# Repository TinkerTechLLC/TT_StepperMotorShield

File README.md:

# TT_StepperMotorShield
This stepper motor shield is capable of smooth, simultaneous control of two bi-polar stepper using [Allegro A4988 
stepper driver breakout sticks](https://www.pololu.com/product/1182). It also has a handy mounting location for an 
[XBee radio adapter board](https://www.adafruit.com/products/126). Use caution when using the XBee radio at the 
same time as the motors. It has been found to cause hiccups in the motors step interrupts, so this can cause the motors
to stall when running at higher speeds.

Order boards here: https://oshpark.com/shared_projects/M8zwapGA

Library for controller shield via Arduino Uno: https://github.com/TinkerTechLLC/TT_StepperMotorShield_Library

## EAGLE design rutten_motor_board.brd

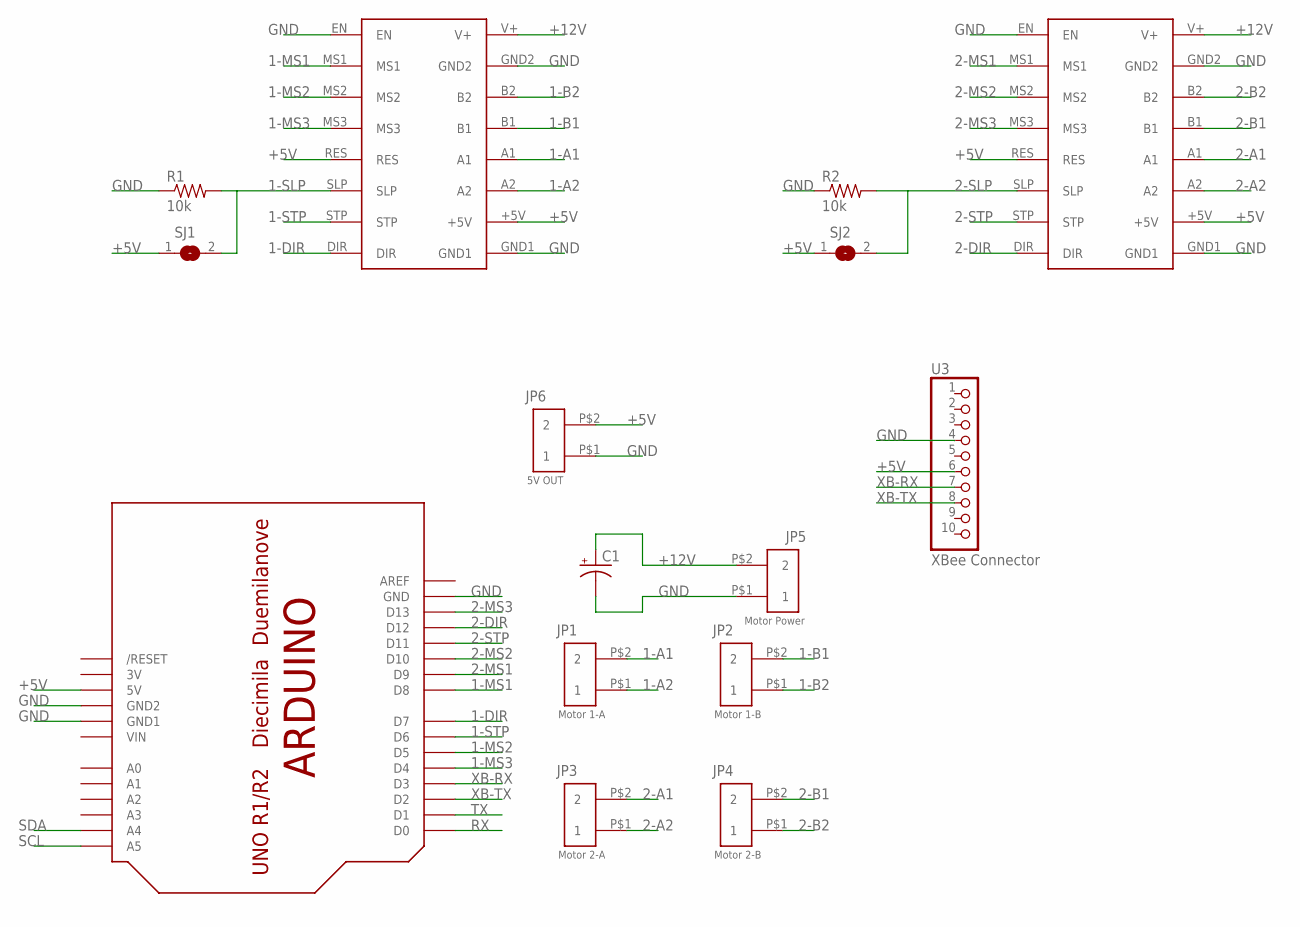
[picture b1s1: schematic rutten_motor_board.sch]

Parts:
C1: CAP_POLPTH2; CPOL-RADIAL-10UF-25V
JP1: Motor 1-A; SCREW_TERM-200MIL-2
JP2: Motor 1-B; SCREW_TERM-200MIL-2
JP3: Motor 2-A; SCREW_TERM-200MIL-2
JP4: Motor 2-B; SCREW_TERM-200MIL-2
JP5: Motor Power; SCREW_TERM-200MIL-2
JP6: 5V OUT; SCREW_TERM-200MIL-2
R1, R2: 10k; AXIAL-0.4
SJ1, SJ2: SJ
U1, U2: A4988_STEP_STICK; A9488_STEP_STICK
U3: XBee Connector; 1X10-BIG
U$1: ARDUINOUNO; ARDUINO

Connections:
1-A1: JP1.P$2 (2), U1.A1
1-A2: JP1.P$1 (1), U1.A2
1-B1: JP2.P$2 (2), U1.B1
1-B2: JP2.P$1 (1), U1.B2
1-DIR: U1.DIR, U$1.D7
1-MS1: U1.MS1, U$1.D8
1-MS2: U1.MS2, U$1.D5
1-MS3: U1.MS3, U$1.D4
1-SLP: R1.P$2 (2), SJ1.2, U1.SLP
1-STP: U1.STP, U$1.D6
2-A1: JP3.P$2 (2), U2.A1
2-A2: JP3.P$1 (1), U2.A2
2-B1: JP4.P$2 (2), U2.B1
2-B2: JP4.P$1 (1), U2.B2
2-DIR: U2.DIR, U$1.D12
2-MS1: U2.MS1, U$1.D9
2-MS2: U2.MS2, U$1.D10
2-MS3: U2.MS3, U$1.D13
2-SLP: R2.P$2 (2), SJ2.2, U2.SLP
2-STP: U2.STP, U$1.D11
5V: U$1.3V
+5V: JP6.P$2 (2), SJ1.1, SJ2.1, U1.+5V, U1.RES, U2.+5V, U2.RES, U3.6, U$1.5V
+12V: C1.1 (+), JP5.P$2 (2), U1.V+, U2.V+
GND: C1.2 (-), JP5.P$1 (1), JP6.P$1 (1), R1.P$1 (1), R2.P$1 (1), U1.EN, U1.GND1, U1.GND2, U2.EN, U2.GND1, U2.GND2, U3.4, U$1.GND, U$1.GND1, U$1.GND2
RX: U$1.D0
SCL: U$1.A5
SDA: U$1.A4
TX: U$1.D1
VIN: U$1.VIN
XB-RX: U3.7, U$1.D3
XB-TX: U3.8, U$1.D2

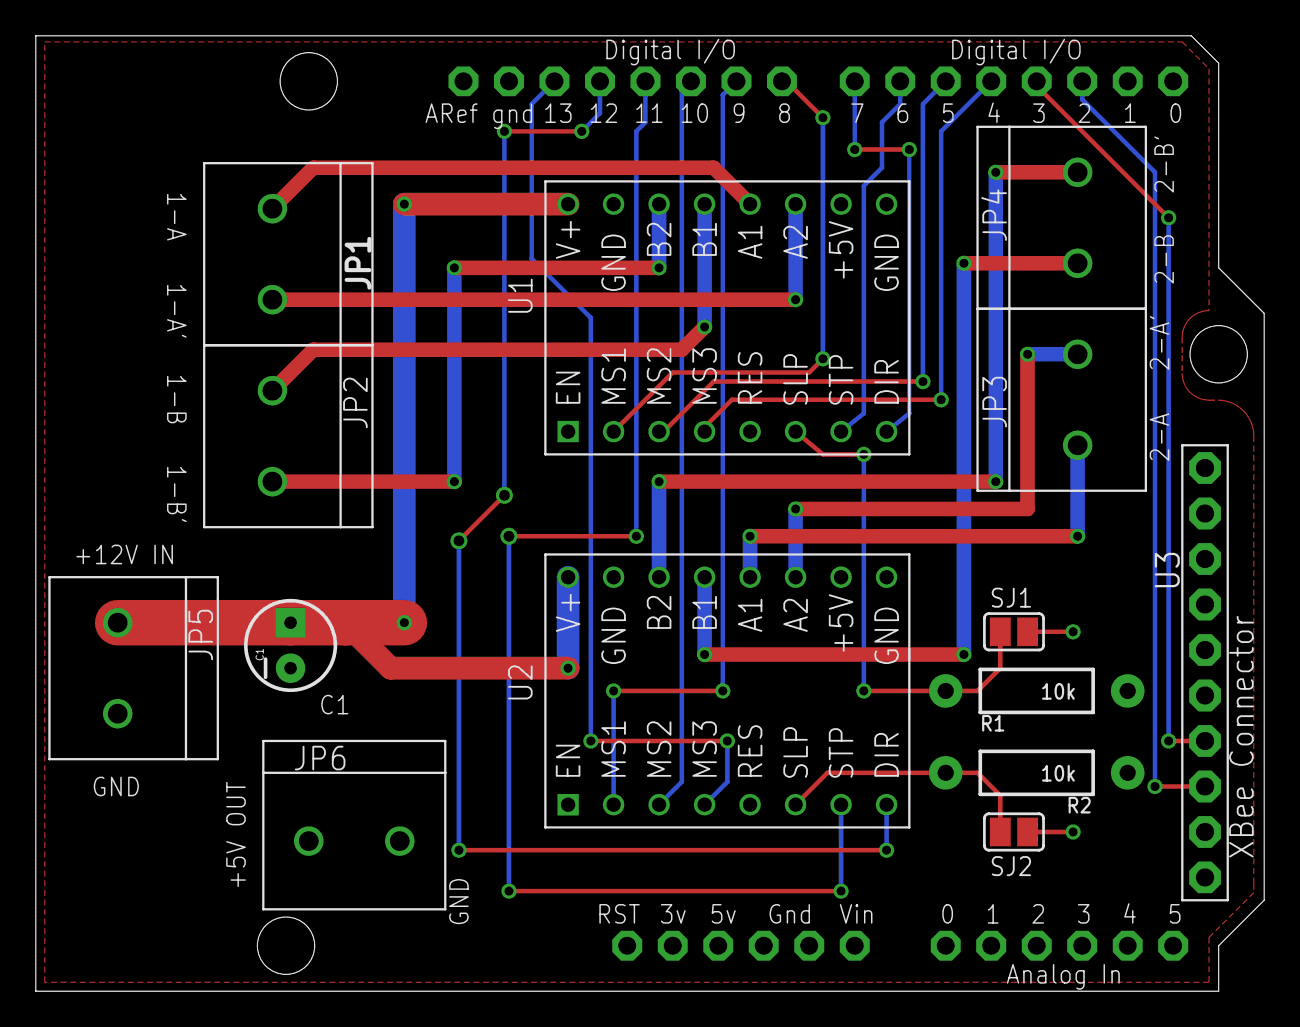
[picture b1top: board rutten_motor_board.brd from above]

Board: 2 copper layers, 68.6 x 53.3 mm, 15 parts (0 on the bottom side), 25 nets.

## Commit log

2016-06-20 :boom::camel: Added .gitattributes & .gitignore files
2016-06-20 Finalized layout

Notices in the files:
parts and their libraries:
SparkFun-Passives: Licensing: Creative Commons ShareAlike 4.0 International - https://creativecommons.org/licenses/by-sa/4.0
